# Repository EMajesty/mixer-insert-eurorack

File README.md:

10HP module for interfacing mixer inserts to eurorack, with a cursed perfboard layout

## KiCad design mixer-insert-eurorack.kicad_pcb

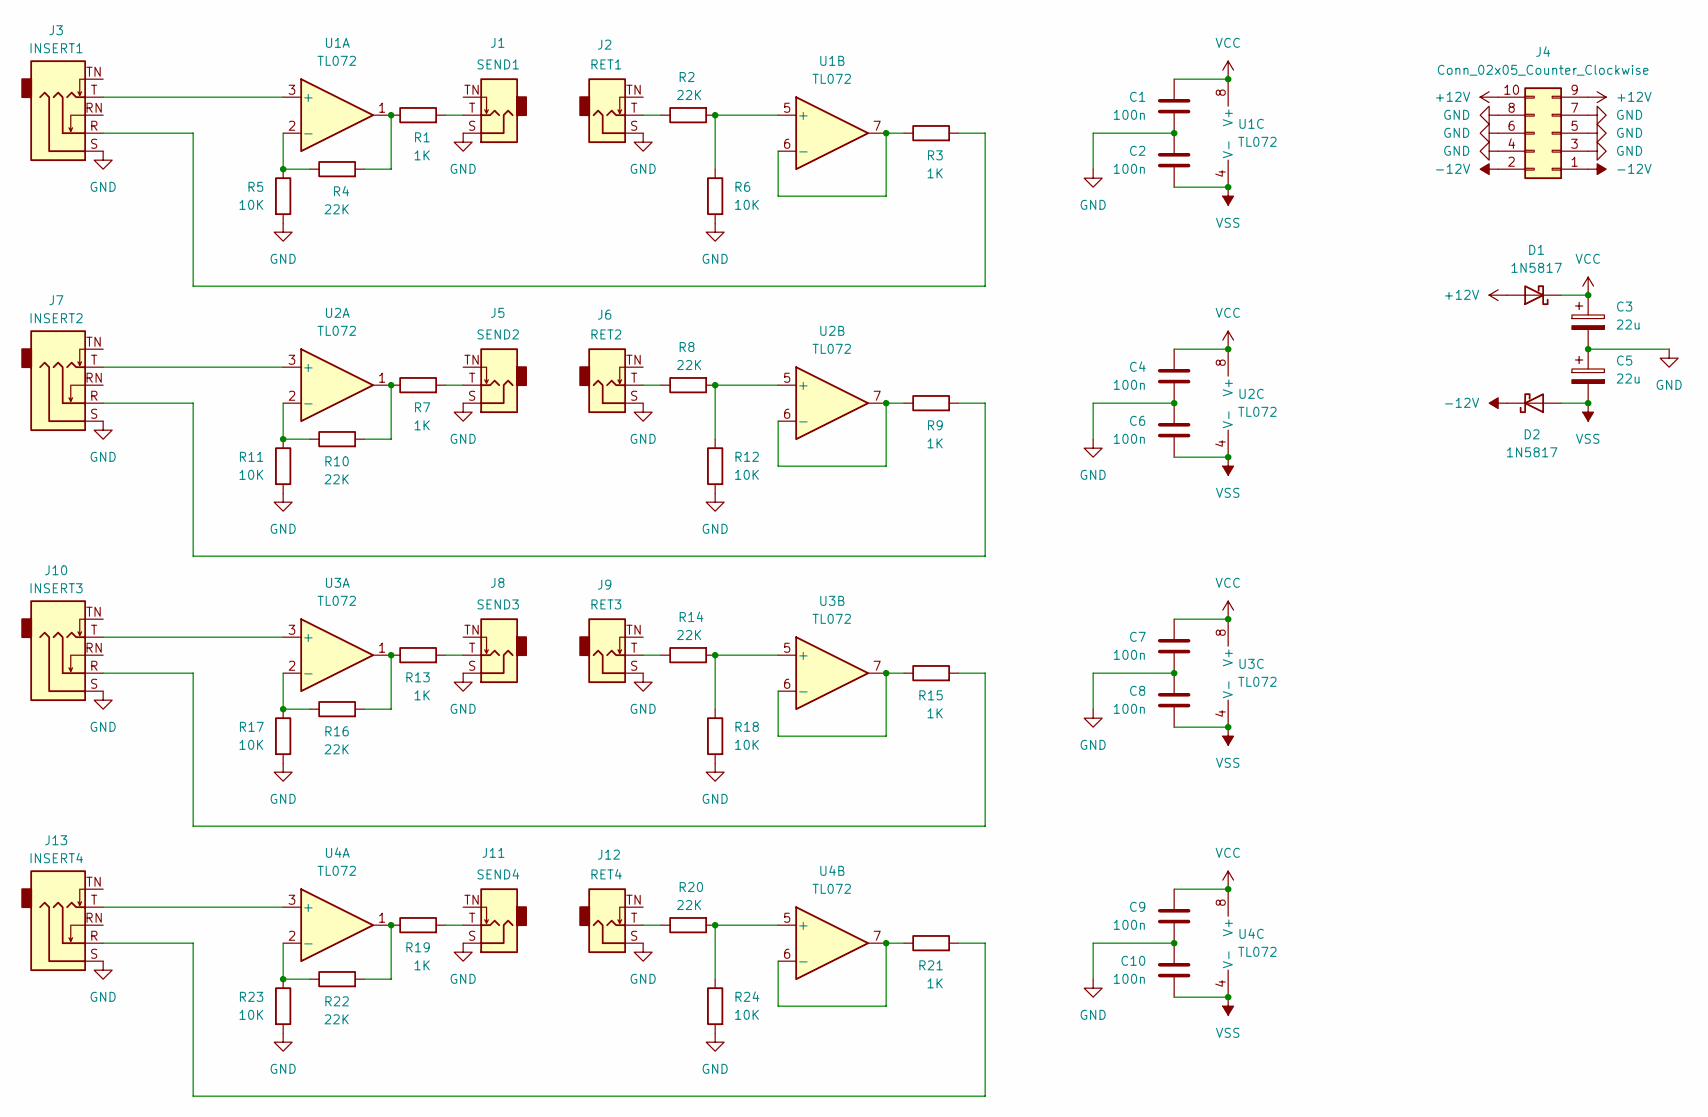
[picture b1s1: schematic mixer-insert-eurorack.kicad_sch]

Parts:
C1, C2, C4, C6, C7, C8, C9, C10: 100n; C_Rect_L7.0mm_W2.5mm_P5.00mm
C3, C5: 22u; CP_Radial_D5.0mm_P2.50mm
D1, D2: 1N5817; D_T-1_P5.08mm_Horizontal
J1: SEND1; Jack_3.5mm_QingPu_WQP-PJ398SM_Vertical_CircularHoles
J2: RET1; Jack_3.5mm_QingPu_WQP-PJ398SM_Vertical_CircularHoles
J3: INSERT1; Jack_6.35mm_Neutrik_NJ5FD-V_Vertical
J4: Conn_02x05_Counter_Clockwise; PinHeader_2x05_P2.54mm_Horizontal
J5: SEND2; Jack_3.5mm_QingPu_WQP-PJ398SM_Vertical_CircularHoles
J6: RET2; Jack_3.5mm_QingPu_WQP-PJ398SM_Vertical_CircularHoles
J7: INSERT2; Jack_6.35mm_Neutrik_NJ5FD-V_Vertical
J8: SEND3; Jack_3.5mm_QingPu_WQP-PJ398SM_Vertical_CircularHoles
J9: RET3; Jack_3.5mm_QingPu_WQP-PJ398SM_Vertical_CircularHoles
J10: INSERT3; Jack_6.35mm_Neutrik_NJ5FD-V_Vertical
J11: SEND4; Jack_3.5mm_QingPu_WQP-PJ398SM_Vertical_CircularHoles
J12: RET4; Jack_3.5mm_QingPu_WQP-PJ398SM_Vertical_CircularHoles
J13: INSERT4; Jack_6.35mm_Neutrik_NJ5FD-V_Vertical
R1, R3, R7, R9, R13, R15, R19, R21: 1K; R_Axial_DIN0207_L6.3mm_D2.5mm_P7.62mm_Horizontal
R2, R4, R8, R10, R14, R16, R20, R22: 22K; R_Axial_DIN0207_L6.3mm_D2.5mm_P7.62mm_Horizontal
R5, R6, R11, R12, R17, R18, R23, R24: 10K; R_Axial_DIN0207_L6.3mm_D2.5mm_P7.62mm_Horizontal
U1, U2, U3, U4: TL072; DIP-8_W7.62mm

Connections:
+12V: D1.2 (A), J4.9, J4.10
-12V: D2.1 (K), J4.1, J4.2
GND: C1.2, C2.1, C3.2, C4.2, C5.1, C6.1, C7.2, C8.1, C9.2, C10.1, J1.S, J2.S, J3.S, J4.3, J4.4, J4.5, J4.6, J4.7, J4.8, J5.S, J6.S, J7.S, J8.S, J9.S, J10.S, J11.S, J12.S, J13.S, R5.2, R6.2, R11.2, R12.2, R17.2, R18.2, R23.2, R24.2
unnamed: J1.T, R1.2
unnamed: J2.T, R2.1
unnamed: J3.R, R3.2
unnamed: J5.T, R7.2
unnamed: J6.T, R8.1
unnamed: J7.R, R9.2
unnamed: J8.T, R13.2
unnamed: J9.T, R14.1
unnamed: J10.R, R15.2
unnamed: J11.T, R19.2
unnamed: J12.T, R20.1
unnamed: J13.R, R21.2
unnamed: R1.1, R4.2, U1.1
unnamed: R7.1, R10.2, U2.1
unnamed: R13.1, R16.2, U3.1
unnamed: R19.1, R22.2, U4.1
unnamed: J3.T, U1.3 (+)
unnamed: R4.1, R5.1, U1.2 (-)
unnamed: R2.2, R6.1, U1.5 (+)
unnamed: R3.1, U1.6 (-), U1.7
unnamed: J7.T, U2.3 (+)
unnamed: R10.1, R11.1, U2.2 (-)
unnamed: R8.2, R12.1, U2.5 (+)
unnamed: R9.1, U2.6 (-), U2.7
unnamed: J10.T, U3.3 (+)
unnamed: R16.1, R17.1, U3.2 (-)
unnamed: R14.2, R18.1, U3.5 (+)
unnamed: R15.1, U3.6 (-), U3.7
unnamed: J13.T, U4.3 (+)
unnamed: R22.1, R23.1, U4.2 (-)
unnamed: R20.2, R24.1, U4.5 (+)
unnamed: R21.1, U4.6 (-), U4.7
VCC: C1.1, C3.1, C4.1, C7.1, C9.1, D1.1 (K), U1.8 (V+), U2.8 (V+), U3.8 (V+), U4.8 (V+)
VSS: C2.2, C5.2, C6.2, C8.2, C10.2, D2.2 (A), U1.4 (V-), U2.4 (V-), U3.4 (V-), U4.4 (V-)

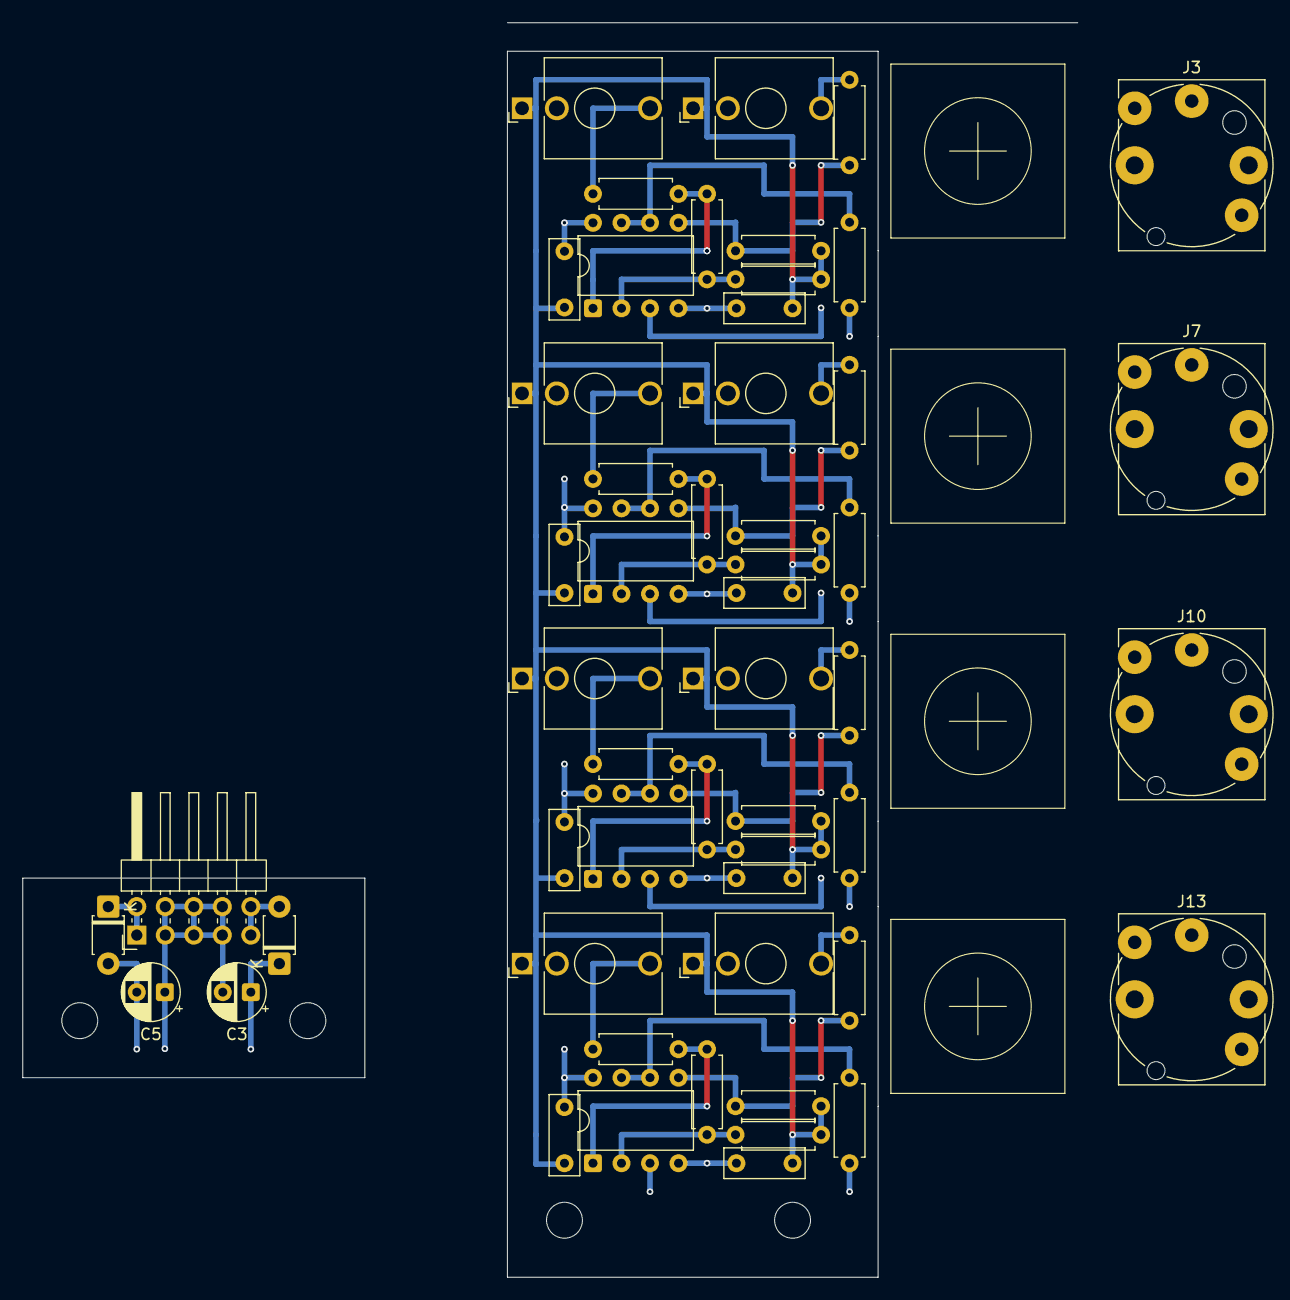
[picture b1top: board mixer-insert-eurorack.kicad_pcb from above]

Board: 2 copper layers, 33.0 x 109.2 mm, 53 parts (0 on the bottom side), 37 nets.
